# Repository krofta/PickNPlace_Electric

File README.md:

In general this repo contains all pcb schematics and layouts to build a simple
pick and place machine. All components are 24V compatible 
 
This repo contains the development of a computer vision modul
with STM32H7. It works as an automomous modul, wich communicates via can
bus. The images are captured via OV7670 camera. The modul has an external RAM of
8Mb zu make shure enough RAM is acessable to perform image processing.
 
PCB for the feeders:
Feeders are inspired by RepoPNP from Simun Huber:
https://github.com/Scavenger18/RepoPNP

The feeders will get some modification: cheaper micro controller from STmicroelectronics and 
prettier edge cut of the PCB plus mondifications of the drills to have another option to mount 
the procket motor with additional bearing.

Controller Module mith STM32F4 to execute simple reduced GCODE. Not shure if I will use 3D-printing like gcode or 
a very simple own format. The main board is capable to receive commands via virtual com port. 
It communicates with:
-Stepper board via GPIO and single wire
-Computer vision modules via CAN-bus(upside down and downside up) to find fiducials 
 and notice the xy-offset and rotation of an picket IC
-Feeders via CAN-bus

Stepper-Board: Just simple board with 4 Trinamic stepper drivers and connectors

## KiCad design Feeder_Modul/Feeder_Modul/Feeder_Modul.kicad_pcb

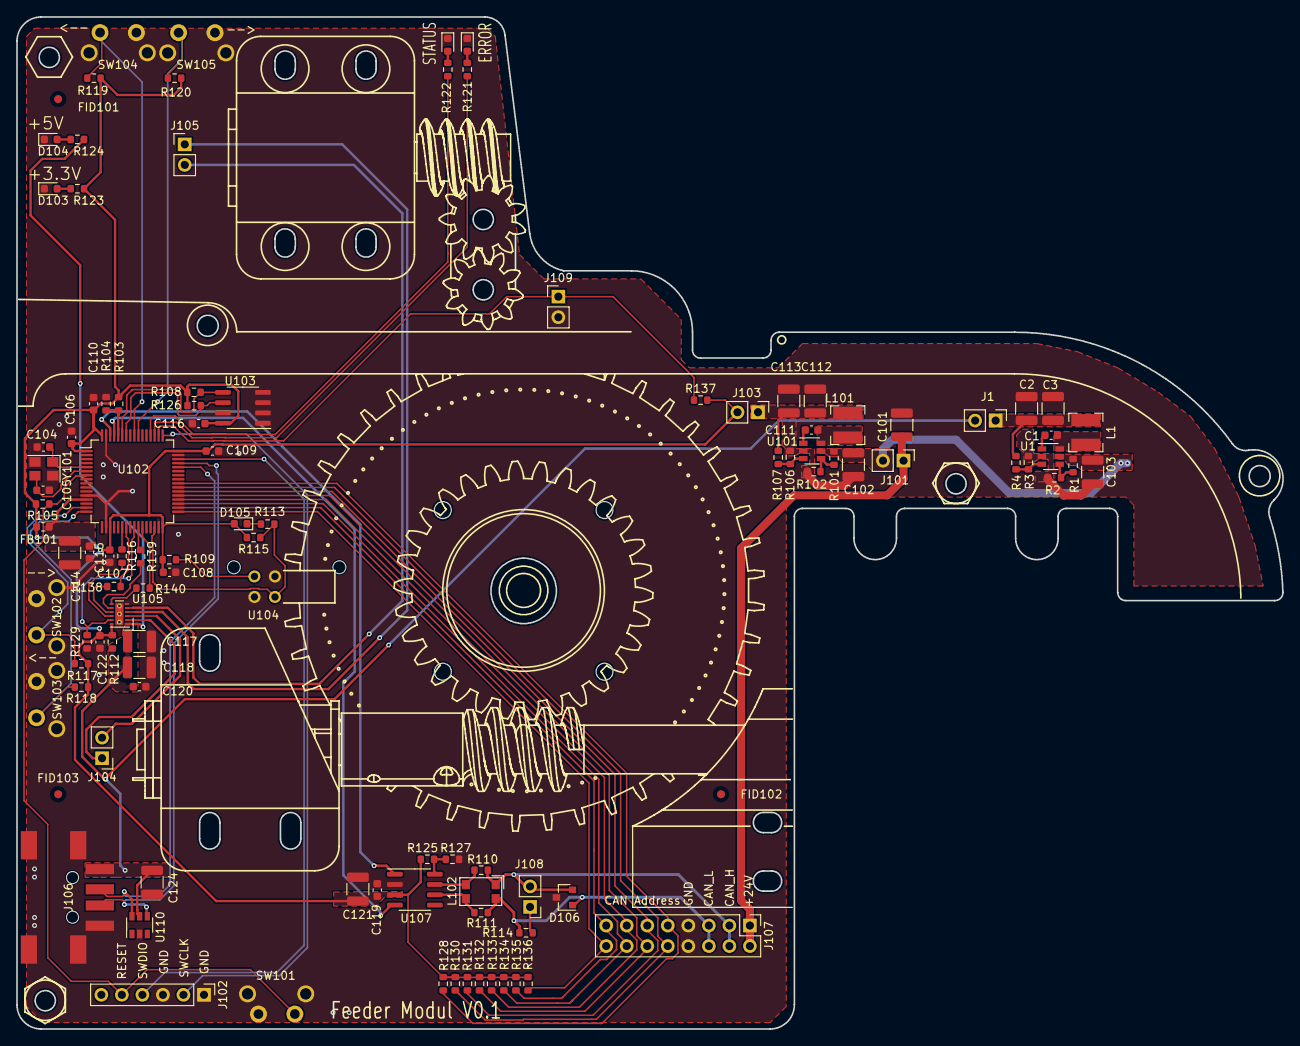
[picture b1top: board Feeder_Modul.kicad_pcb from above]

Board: 2 copper layers, 156.6 x 125.2 mm, 110 parts (0 on the bottom side), 69 nets.

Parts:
C1, C106, C107, C108, C109, C110, C111, C115, C116, C119, C120, C122: 100n 50V; C_0603_1608Metric
C2, C3, C101, C102, C103, C112, C113, C114, C117, C118, C121, C124: 10u 50V; C_1210_3225Metric
C104, C105: 18p; C_0603_1608Metric
D101: LED_red; LED_0603_1608Metric
D102: LED_green; LED_0603_1608Metric
D103, D104, D105: LED_Blue; LED_0603_1608Metric
D106: SM24CANA-02HTG; SOT-23
FB101: 70R; L_0603_1608Metric
FID101, FID102, FID103: Fiducial; Fiducial_1mm_Mask2mm
J1, J101, J103, J104, J105, J108, J109: Conn_02x01; PinHeader_1x02_P2.54mm_Vertical
J102: Conn_01x06_Male; PinHeader_1x06_P2.54mm_Vertical
J106: WE_629104190121; WE629104190121
J107: Conn_02x07_Odd_Even; PinHeader_2x08_P2.54mm_Vertical
L1, L101: 12u SRN4018; L_Bourns-SRN4018
L102: DNP; L_CommonModeChoke_Coilcraft_1812CAN
R1, R2, R101, R102, R107: 51K; R_0603_1608Metric
R3, R106: 22K1; R_0603_1608Metric
R4, R128, R130, R131, R132, R133, R134, R135, R136: 88K7; R_0603_1608Metric
R103, R112, R125: DNP; R_0603_1608Metric
R104, R105, R115, R117, R118, R119, R120, R129, R137: 10K; R_0603_1608Metric
R108, R116, R121, R122, R123, R124, R126, R127, R138, R139, R140: 1k; R_0603_1608Metric
R109, R114: 120R; R_0603_1608Metric
R110, R111: 0R; R_0603_1608Metric
R113: 1K; R_0603_1608Metric
SW101, SW102, SW103, SW104, SW105: SW_Push; TactileSwitchLCSC
U1, U101: TPS560430; SOT-23-6
U102: STM32F105R8Tx; LQFP-64_10x10mm_P0.5mm
U103: M24C01-WMN; SOIC-8_3.9x4.9mm_P1.27mm
U104: TCST5250
U105: DRV8835; WSON-12-1EP_3x2mm_P0.5mm_EP1x2.65_ThermalVias
U106: Panasonic_ESE22; Empty
U107: SN65HVD230; SOIC-8_3.9x4.9mm_P1.27mm
U108, U109: N20_DC_Motor; Empty
U110: SRV05-4; SOT-23-6
Y101: 8MHz; Crystal_SMD_3225-4Pin_3.2x2.5mm

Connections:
+3V3: C106.1, C107.2, C108.1, C109.2, C110.1, C116.1, C119.1, C121.1, C122.1, D105.2, FB101.2, J103.2, R103.2, R105.2, R108.2, R109.2, R112.2, R115.2, R117.2, R118.2, R119.2, R120.2, R123.2, R125.2, R126.2, R128.2, R130.2, R131.2, R132.2, R133.2, R134.2, R135.2, R136.2, R137.2, U102.1, U102.19, U102.32, U102.48, U102.64, U103.8, U105.12, U107.3
+5V: C117.1, C118.1, C120.1, C124.1, J1.2, J106.1, R112.1, R124.2, U105.1, U110.5
+24V: C101.1, J101.1, J107.1, J107.2
/ADDR0: J107.9, R128.1, U102.40
/ADDR1: J107.10, R130.1, U102.39
/ADDR2: J107.11, R131.1, U102.38
/ADDR3: J107.12, R132.1, U102.37
/ADDR4: J107.13, R133.1, U102.36
/ADDR5: J107.14, R134.1, U102.35
/ADDR6: J107.15, R135.1, U102.34
/ADDR7: J107.16, R136.1, U102.33
/BTN_SBACK: R119.1, SW104.2, U102.56
/BTN_SFOR: R120.1, SW105.2, U102.55
/BTN_TBACK: R117.1, SW102.2, U102.15
/BTN_TFOR: R118.1, SW103.2, U102.16
/CAN1_H: D106.2, J107.3, J107.4, J108.2, L102.2, R110.1
/CAN1_L: D106.1, J107.5, J107.6, L102.4, R111.2, R114.2
/CAN1_RX: U102.61, U107.4
/CAN1_TX: U102.62, U107.1
/ENC_OUT: R113.1, R115.1, U102.30, U104.4
/I2C1_SCL: R126.1, U102.58, U103.6
/I2C1_SDA: R108.1, U102.59, U103.5
/LED_error: R121.2, U102.51
/LED_status: R122.2, U102.52
/MODE: R129.2, U102.25, U105.11
/NRST: J102.5, R105.1, SW101.2, U102.7
/PA6: R116.2, U102.22
/PA7: R138.1, U102.23
/PA13: J102.4, U102.46
/PA14: J102.2, U102.49
/PD0: C104.1, U102.5, Y101.1
/PD1: C105.1, U102.6, Y101.3
/PWM_A: R116.1, U105.10
/PWM_B: R138.2, U105.9
/PWM_C: R139.1, U105.8
/PWM_D: R140.2, U105.7
/SprocketMotor+: J104.1, U105.2
/SprocketMotor-: J104.2, U105.3
/TAPE_MICROBTN: J109.1, R137.1, U102.50
/TIM3_CH3: R139.2, U102.26
/TIM3_CH4: R140.1, U102.27
/TapeMotor+: J105.1, U105.4
/TapeMotor-: J105.2, U105.5
/USB_OTG+: J106.3, U102.45, U110.4
/USB_OTG-: J106.2, U102.44, U110.6
GND: C2.2, C3.2, C101.2, C102.2, C103.2, C104.2, C105.2, C106.2, C107.1, C108.2, C109.1, C110.2, C112.2, C113.2, C114.2, C115.2, C116.2, C117.2, C118.2, C119.2, C120.2, C121.2, C122.2, C124.2, D101.1, D102.1, D103.1, D104.1, D106.3, J102.1, J102.3, J106.4, J106.5, J107.7, J107.8, J109.2, R2.1, R3.1, R102.1, R104.2, R106.1, R127.1, R129.1, SW101.1, SW101.3, SW102.1, SW102.3, SW103.1, SW103.3, SW104.1, SW104.3, SW105.1, SW105.3, U1.2, U101.2, U102.12, U102.18, U102.31, U102.47, U102.63, U103.1, U103.2, U103.3, U103.4, U103.7, U104.2, U104.3, U105.6, U105.13, U107.2, U110.2, Y101.2, Y101.4
unnamed: C1.1, L1.1, U1.6
unnamed: C1.2, U1.1
unnamed: C2.1, C3.1, J1.1, L1.2, R4.2
unnamed: C102.1, C103.1, J101.2, R1.1, R101.1, U1.5, U101.5
unnamed: C111.1, L101.1, U101.6
unnamed: C111.2, U101.1
unnamed: C112.1, C113.1, J103.1, L101.2, R107.2
unnamed: C114.1, C115.1, FB101.1, U102.13
unnamed: D101.2, R121.1
unnamed: D102.2, R122.1
unnamed: D103.2, R123.1
unnamed: D104.2, R124.1
unnamed: D105.1, R113.2
unnamed: J108.1, R114.1
unnamed: L102.1, R110.2, U107.7
unnamed: L102.3, R111.1, U107.6
unnamed: R1.2, R2.2, U1.4
unnamed: R3.2, R4.1, U1.3
unnamed: R101.2, R102.2, U101.4
unnamed: R103.1, R104.1, U102.60
unnamed: R106.2, R107.1, U101.3
unnamed: R109.1, U104.1
unnamed: R125.1, R127.2, U107.8

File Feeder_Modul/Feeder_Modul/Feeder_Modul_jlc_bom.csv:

Comment,Designator,Footprint,LCSC Part #
"100n 50V Unpolarized capacitor, small symbol","C1,C106,C107,C108,C109,C110,C111,C115,C116,C119,C120,C122",C_0603_1608Metric,C282519
"10u 50V Unpolarized capacitor, small symbol","C2,C3,C101,C102,C103,C112,C113,C114,C117,C118,C121,C124",C_1210_3225Metric,C1849
"18p Unpolarized capacitor, small symbol","C104,C105",C_0603_1608Metric,C258467
"LED_red Light emitting diode, small symbol",D101,LED_0603_1608Metric,C118330
"LED_green Light emitting diode, small symbol",D102,LED_0603_1608Metric,C205443
"LED_Blue Light emitting diode, small symbol","D103,D104,D105",LED_0603_1608Metric,C192317
"70R Ferrite bead, small symbol",FB101,L_0603_1608Metric,C513774
"Conn_02x01 Generic connector, single row, 01x02, script generated (kicad-library-utils/schlib/autogen/connector/)","J1,J101,J103,J104,J105,J108,J109",PinHeader_1x02_P2.54mm_Vertical,C358684
WE_629104190121 ,J106,WE629104190121,C718026
"Conn_02x07_Odd_Even Generic connector, double row, 02x07, odd/even pin numbering scheme (row 1 odd numbers, row 2 even numbers), script generated (kicad-library-utils/schlib/autogen/connector/)",J107,PinHeader_2x07_P2.54mm_Horizontal,C146608
"12u  SRN4018 Inductor, small symbol","L1,L101",L_Bourns-SRN4018,C354591 
"51K Resistor, small symbol","R1,R2,R101,R102,R107",R_0603_1608Metric,C384211
"22K1 Resistor, small symbol","R3,R106",R_0603_1608Metric,C137768
"88K7 Resistor, small symbol","R4,R128,R130,R131,R132,R133,R134,R135,R136",R_0603_1608Metric,C163418
"10K Resistor, small symbol","R104,R105,R115,R117,R118,R119,R120,R129,R137",R_0603_1608Metric,C99198
"1k Resistor, small symbol","R108,R109,R121,R122,R123,R124,R126,R127",R_0603_1608Metric,C21190
"0R Resistor, small symbol","R110,R111",R_0603_1608Metric,C384298
"1K Resistor, small symbol",R113,R_0603_1608Metric,C21190
"120R Resistor, small symbol",R114,R_0603_1608Metric,C114681
"SW_Push Push button switch, generic, two pins","SW101,SW102,SW103,SW104,SW105",TactileSwitchLCSC,C455137
TPS560430 ,"U1,U101",SOT-23-6,C524782
"STM32F105R8Tx ARM Cortex-M3 MCU, 64KB flash, 64KB RAM, 72MHz, 2-3.6V, 51 GPIO, LQFP-64",U102,LQFP-64_10x10mm_P0.5mm,C80986
"M24C01-WMN 1Kb (128x8) I2C Serial EEPROM, 2.5-5.5V, SOIC-8",U103,SOIC-8_3.9x4.9mm_P1.27mm,C7996
DRV8835 ,U105,WSON-12-1EP_3x2mm_P0.5mm_EP1x2.65_ThermalVias,C129328
"SN65HVD230 CAN Bus Transceivers, 3.3V, 1Mbps, Low-Power capabilities, SOIC-8",U107,SOIC-8_3.9x4.9mm_P1.27mm,C12084
"48MHz Four pin crystal, GND on pins 2 and 4",Y101,Crystal_SMD_3225-4Pin_3.2x2.5mm,C389928

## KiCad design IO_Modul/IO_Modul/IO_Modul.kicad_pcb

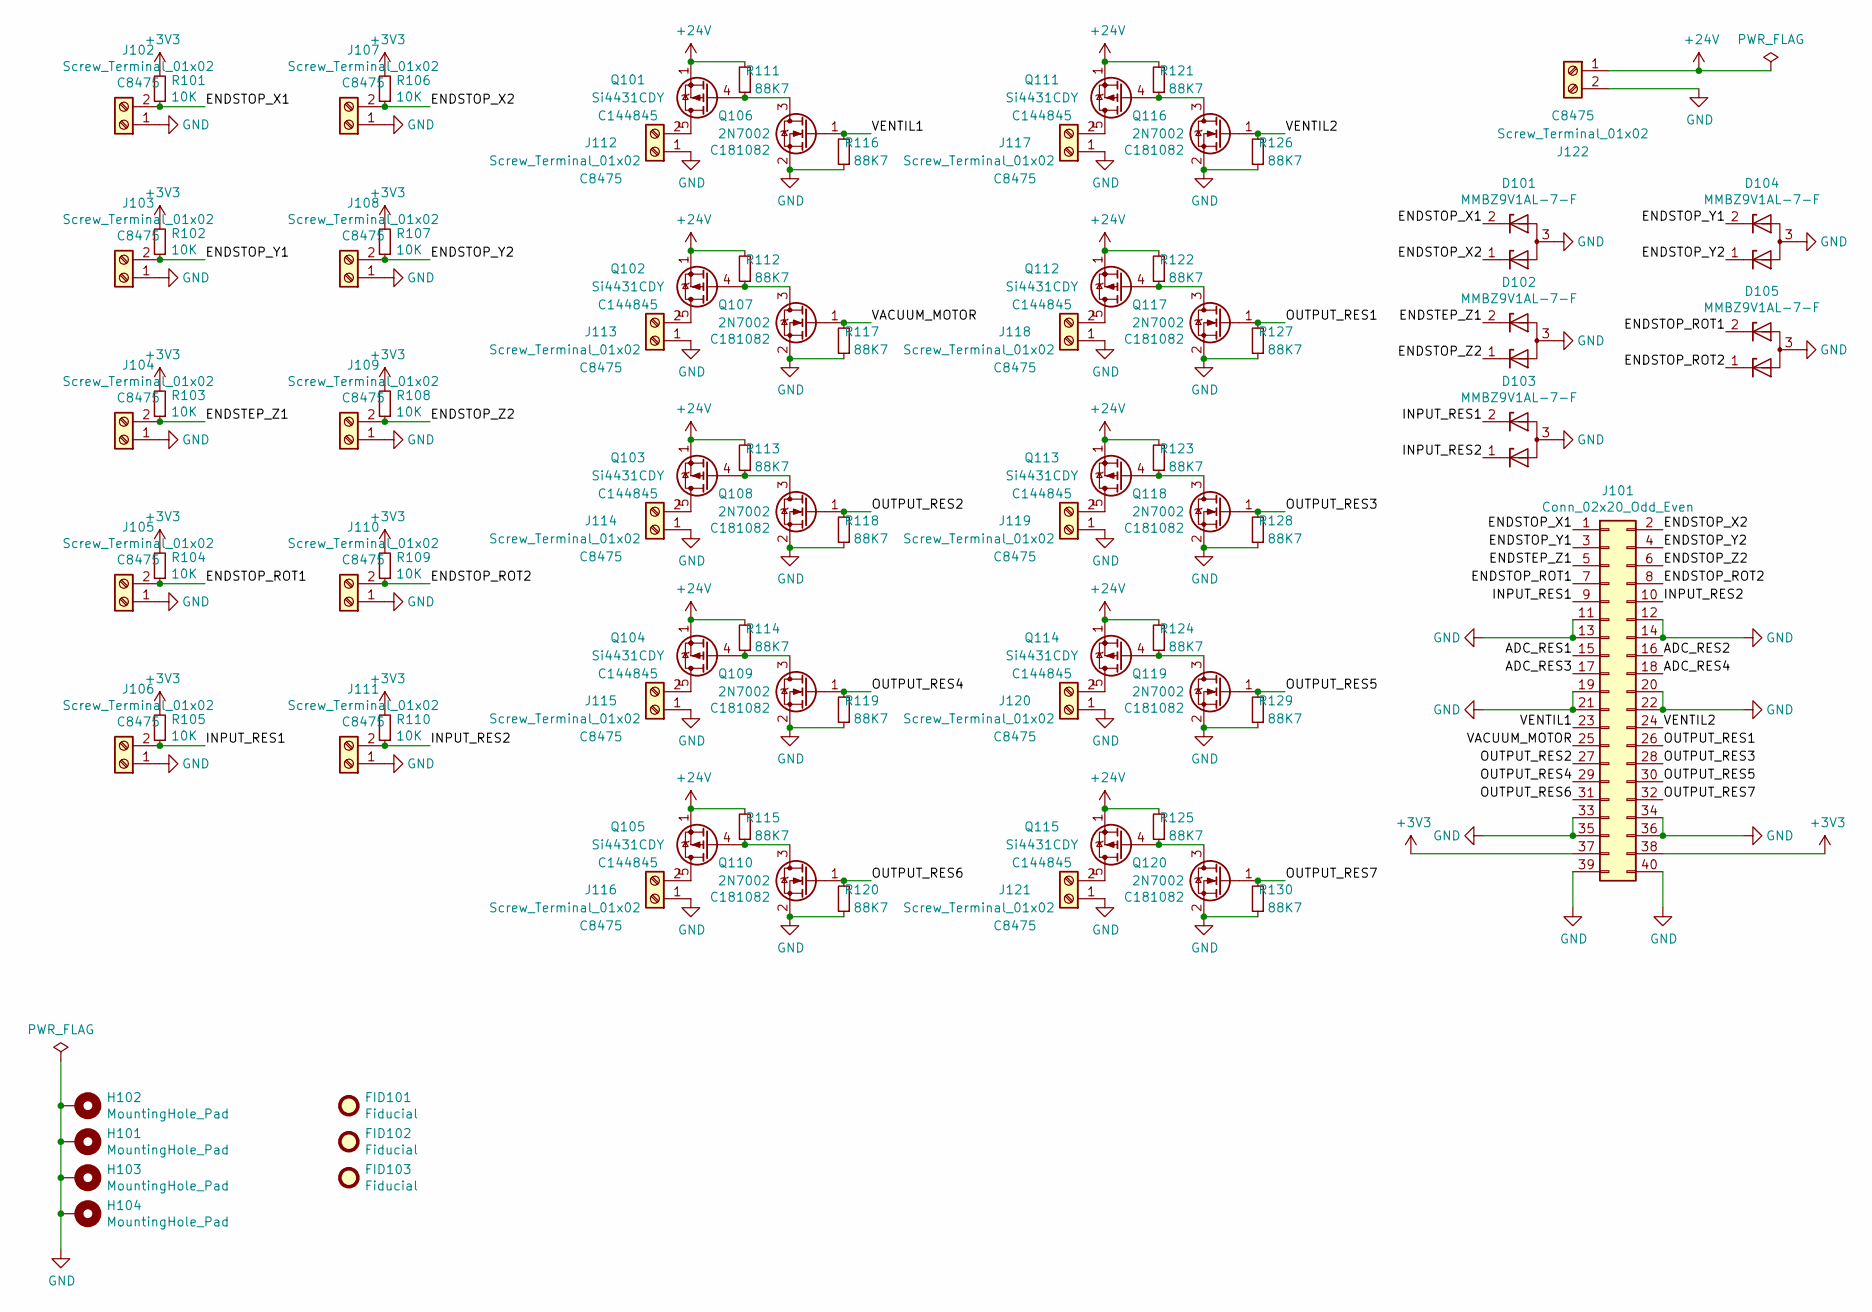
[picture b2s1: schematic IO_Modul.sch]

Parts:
D101, D102, D103, D104, D105: MMBZ9V1AL-7-F; SOT-23; LCSC C460913
FID101, FID102, FID103: Fiducial; Fiducial_1mm_Mask2mm
H101, H102, H103, H104: MountingHole_Pad; MountingHole_3.2mm_M3_Pad_Via; LCSC 0
J101: Conn_02x20_Odd_Even; PinHeader_2x20_P2.54mm_Vertical; LCSC C601944
J102, J103, J104, J105, J106, J107, J108, J109, J110, J111, J112, J113, J114, J115, J116, J117, J118, J119, J120, J121, J122: Screw_Terminal_01x02; TerminalBlock_RND_205-00045_1x02_P5.00mm_Horizontal; LCSC C8475
Q101, Q102, Q103, Q104, Q105, Q111, Q112, Q113, Q114, Q115: Si4431CDY; SOIC-8_3.9x4.9mm_P1.27mm; LCSC C144845
Q106, Q107, Q108, Q109, Q110, Q116, Q117, Q118, Q119, Q120: 2N7002; SOT-23; LCSC C181082
R101, R102, R103, R104, R105, R106, R107, R108, R109, R110: 10K; R_0603_1608Metric; LCSC C99198
R111, R112, R113, R114, R115, R116, R117, R118, R119, R120, R121, R122, R123, R124, R125, R126, R127, R128, R129, R130: 88K7; R_0603_1608Metric; LCSC C163418

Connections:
+3V3: J101.37, J101.38, R101.2, R102.2, R103.2, R104.2, R105.2, R106.2, R107.2, R108.2, R109.2, R110.2; also elsewhere on the board
+24V: J122.1, Q101.1 (D), Q101.2 (D), Q101.3 (D), Q102.1 (D), Q102.2 (D), Q102.3 (D), Q103.1 (D), Q103.2 (D), Q103.3 (D), Q104.1 (D), Q104.2 (D), Q104.3 (D), Q105.1 (D), Q105.2 (D), Q105.3 (D), Q111.1 (D), Q111.2 (D), Q111.3 (D), Q112.1 (D), Q112.2 (D), Q112.3 (D), Q113.1 (D), Q113.2 (D), Q113.3 (D), Q114.1 (D), Q114.2 (D), Q114.3 (D), Q115.1 (D), Q115.2 (D), Q115.3 (D), R111.2, R112.2, R113.2, R114.2, R115.2, R121.2, R122.2, R123.2, R124.2, R125.2
/ADC_RES1: J101.15; also elsewhere on the board
/ADC_RES2: J101.16; also elsewhere on the board
/ADC_RES3: J101.17; also elsewhere on the board
/ADC_RES4: J101.18; also elsewhere on the board
/ENDSTEP_Z1: D102.2 (K), J101.5, J104.2, R103.1
/ENDSTOP_ROT1: D105.2 (K), J101.7, J105.2, R104.1
/ENDSTOP_ROT2: D105.1 (K), J101.8, J110.2, R109.1
/ENDSTOP_X1: D101.2 (K), J101.1, J102.2, R101.1
/ENDSTOP_X2: D101.1 (K), J101.2, J107.2, R106.1
/ENDSTOP_Y1: D104.2 (K), J101.3, J103.2, R102.1
/ENDSTOP_Y2: D104.1 (K), J101.4, J108.2, R107.1
/ENDSTOP_Z2: D102.1 (K), J101.6, J109.2, R108.1
/INPUT_RES1: D103.2 (K), J101.9, J106.2, R105.1
/INPUT_RES2: D103.1 (K), J101.10, J111.2, R110.1
/OUTPUT_RES1: J101.26, Q117.1 (G), R127.2
/OUTPUT_RES2: J101.27, Q108.1 (G), R118.2
/OUTPUT_RES3: J101.28, Q118.1 (G), R128.2
/OUTPUT_RES4: J101.29, Q109.1 (G), R119.2
/OUTPUT_RES5: J101.30, Q119.1 (G), R129.2
/OUTPUT_RES6: J101.31, Q110.1 (G), R120.2
/OUTPUT_RES7: J101.32, Q120.1 (G), R130.2
/VACUUM_MOTOR: J101.25, Q107.1 (G), R117.2
/VENTIL1: J101.23, Q106.1 (G), R116.2
/VENTIL2: J101.24, Q116.1 (G), R126.2
GND: D101.3 (A), D102.3 (A), D103.3 (A), D104.3 (A), D105.3 (A), H101.1, H102.1, H103.1, H104.1, J101.11, J101.12, J101.13, J101.14, J101.19, J101.20, J101.21, J101.22, J101.33, J101.34, J101.35, J101.36, J101.39, J101.40, J102.1, J103.1, J104.1, J105.1, J106.1, J107.1, J108.1, J109.1, J110.1, J111.1, J112.1, J113.1, J114.1, J115.1, J116.1, J117.1, J118.1, J119.1, J120.1, J121.1, J122.2, Q106.2 (S), Q107.2 (S), Q108.2 (S), Q109.2 (S), Q110.2 (S), Q116.2 (S), Q117.2 (S), Q118.2 (S), Q119.2 (S), Q120.2 (S), R116.1, R117.1, R118.1, R119.1, R120.1, R126.1, R127.1, R128.1, R129.1, R130.1; also elsewhere on the board
unnamed: J112.2, Q101.5 (S), Q101.6 (S), Q101.7 (S), Q101.8 (S)
unnamed: J113.2, Q102.5 (S), Q102.6 (S), Q102.7 (S), Q102.8 (S)
unnamed: J114.2, Q103.5 (S), Q103.6 (S), Q103.7 (S), Q103.8 (S)
unnamed: J115.2, Q104.5 (S), Q104.6 (S), Q104.7 (S), Q104.8 (S)
unnamed: J116.2, Q105.5 (S), Q105.6 (S), Q105.7 (S), Q105.8 (S)
unnamed: J117.2, Q111.5 (S), Q111.6 (S), Q111.7 (S), Q111.8 (S)
unnamed: J118.2, Q112.5 (S), Q112.6 (S), Q112.7 (S), Q112.8 (S)
unnamed: J119.2, Q113.5 (S), Q113.6 (S), Q113.7 (S), Q113.8 (S)
unnamed: J120.2, Q114.5 (S), Q114.6 (S), Q114.7 (S), Q114.8 (S)
unnamed: J121.2, Q115.5 (S), Q115.6 (S), Q115.7 (S), Q115.8 (S)
unnamed: Q101.4 (G), Q106.3 (D), R111.1
unnamed: Q102.4 (G), Q107.3 (D), R112.1
unnamed: Q103.4 (G), Q108.3 (D), R113.1
unnamed: Q104.4 (G), Q109.3 (D), R114.1
unnamed: Q105.4 (G), Q110.3 (D), R115.1
unnamed: Q111.4 (G), Q116.3 (D), R121.1
unnamed: Q112.4 (G), Q117.3 (D), R122.1
unnamed: Q113.4 (G), Q118.3 (D), R123.1
unnamed: Q114.4 (G), Q119.3 (D), R124.1
unnamed: Q115.4 (G), Q120.3 (D), R125.1

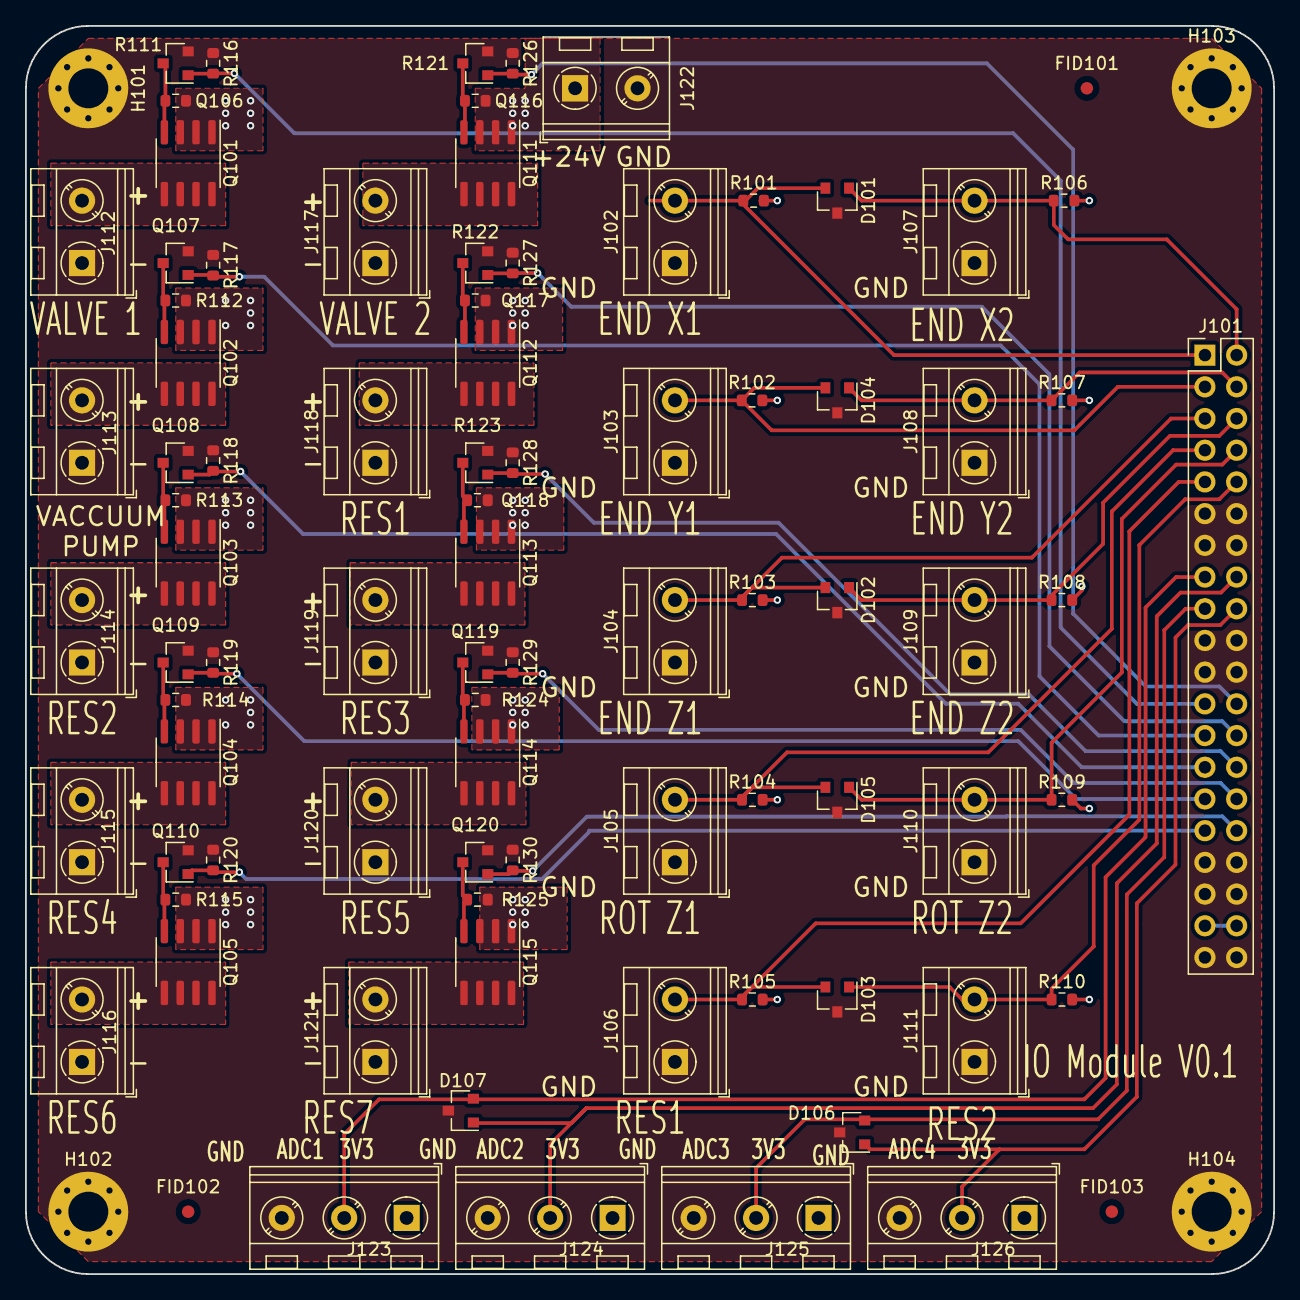
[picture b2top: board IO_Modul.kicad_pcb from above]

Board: 4 copper layers, 100.0 x 100.0 mm, 90 parts (0 on the bottom side), 47 nets.

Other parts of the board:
D106, D107: MMBZ9V1AL-7-F; SOT-23
J123, J124, J125, J126: Screw_Terminal_01x03; TerminalBlock_RND_205-00046_1x03_P5.00mm_Horizontal

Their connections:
+3V3: J123.1, J124.1, J125.1, J126.1; also elsewhere on the board
/ADC_RES1: D107.2, J123.2; also elsewhere on the board
/ADC_RES2: D107.1, J124.2; also elsewhere on the board
/ADC_RES3: D106.2, J125.2; also elsewhere on the board
/ADC_RES4: D106.1, J126.2; also elsewhere on the board
GND: D106.3, D107.3, J123.3, J124.3, J125.3, J126.3; also elsewhere on the board

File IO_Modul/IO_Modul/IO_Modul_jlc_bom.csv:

Comment,Designator,Footprint,LCSC Part #,Quantity
"Conn_02x20_Odd_Even Generic connector, double row, 02x20, odd/even pin numbering scheme (row 1 odd numbers, row 2 even numbers), script generated (kicad-library-utils/schlib/autogen/connector/)",J101,PinHeader_2x20_P2.54mm_Vertical,C601944,1
"Screw_Terminal_01x02 Generic screw terminal, single row, 01x02, script generated (kicad-library-utils/schlib/autogen/connector/)","J102,J103,J104,J105,J106,J107,J108,J109,J110,J111,J112,J113,J114,J115,J116,J117,J118,J119,J120,J121,J122",TerminalBlock_RND_205-00045_1x02_P5.00mm_Horizontal,C8475,21
"Si4431CDY P-MOSFET transistor, drain/gate/source","Q101,Q102,Q103,Q104,Q105,Q111,Q112,Q113,Q114,Q115",SOIC-8_3.9x4.9mm_P1.27mm,C144845,10
"2N7002 0.115A Id, 60V Vds, N-Channel MOSFET, SOT-23","Q106,Q107,Q108,Q109,Q110,Q116,Q117,Q118,Q119,Q120",SOT-23,C181082,10
"10K Resistor, small symbol","R101,R102,R103,R104,R105,R106,R107,R108,R109,R110",R_0603_1608Metric,C99198,10
"88K7 Resistor, small symbol","R111,R112,R113,R114,R115,R116,R117,R118,R119,R120,R121,R122,R123,R124,R125,R126,R127,R128,R129,R130",R_0603_1608Metric,C163418,20

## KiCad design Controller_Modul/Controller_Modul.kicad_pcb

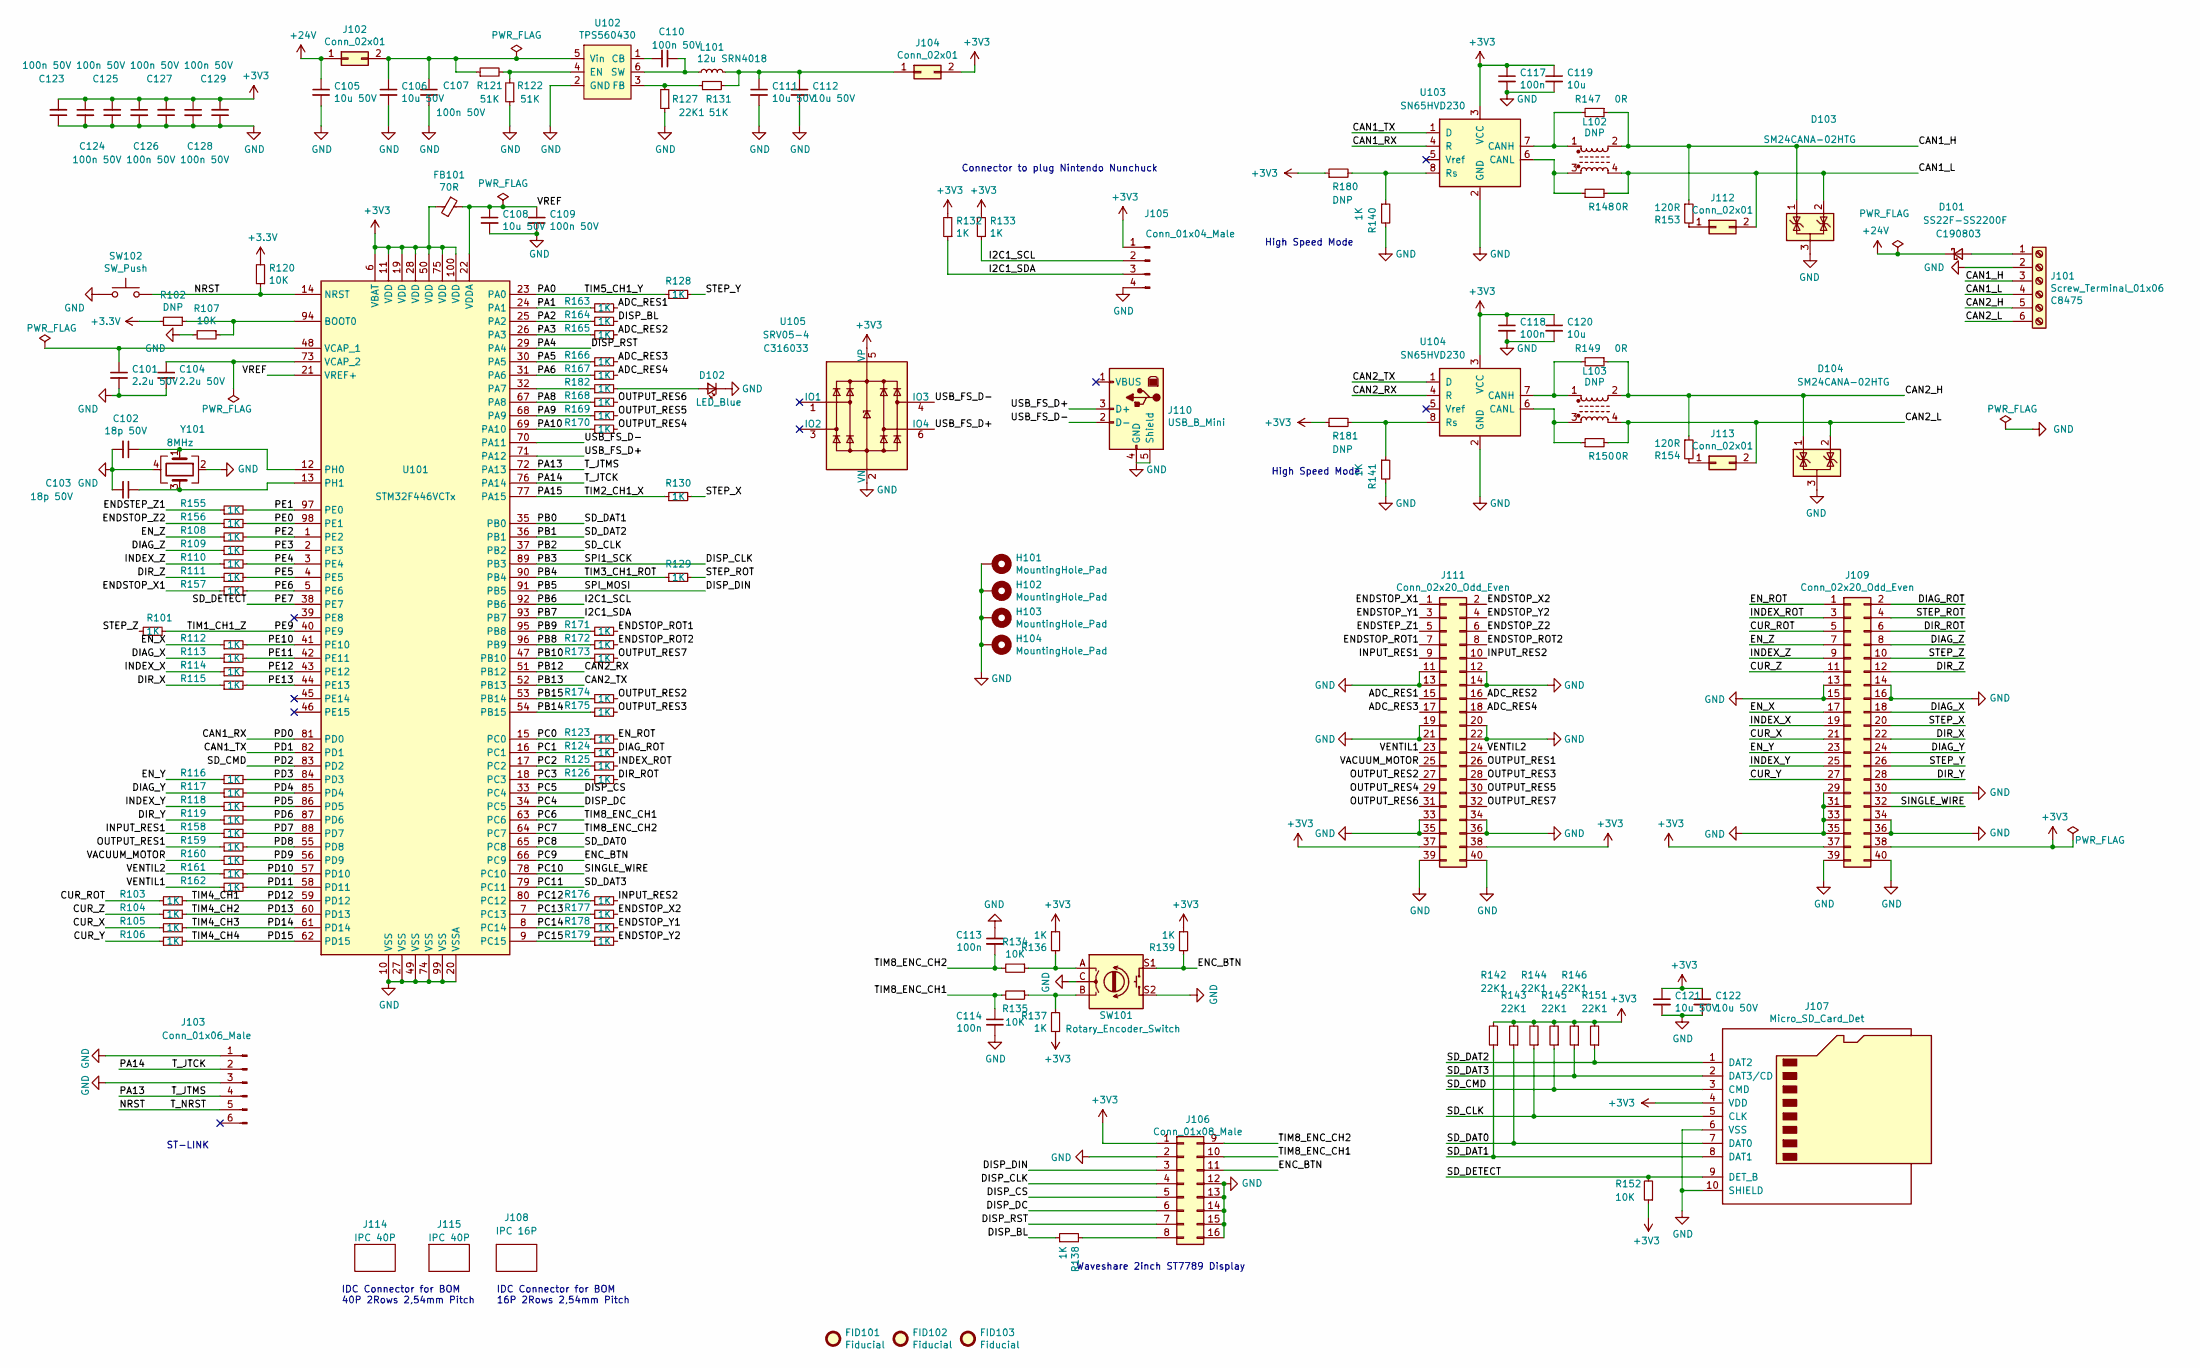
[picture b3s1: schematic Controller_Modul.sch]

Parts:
C101, C104: 2.2u 50V; C_1210_3225Metric; LCSC C696854
C102, C103: 18p 50V; C_0603_1608Metric; LCSC C258467
C105, C106, C108, C111, C112, C121, C122: 10u 50V; C_1210_3225Metric; LCSC C1849
C107, C109, C110, C123, C124, C125, C126, C127, C128, C129: 100n 50V; C_0603_1608Metric; LCSC C282519
C113, C114, C117, C118: 100n; C_0603_1608Metric; LCSC C83060
C119, C120: 10u; C_1210_3225Metric; LCSC C1849
D101: SS22F-SS2200F; D_SMA; LCSC C190803
D102: LED_Blue; LED_0603_1608Metric; LCSC C192317
D103, D104: SM24CANA-02HTG; SOT-23; LCSC C151236
FB101: 70R; L_0603_1608Metric; LCSC C513774
FID101, FID102, FID103: Fiducial; Fiducial_1mm_Mask2mm; LCSC 0
H101, H102, H103, H104: MountingHole_Pad; MountingHole_3.2mm_M3_Pad_Via; LCSC 0
J101: Screw_Terminal_01x06; TerminalBlock_RND_205-00049_1x06_P5.00mm_Horizontal; LCSC C8475
J102, J104, J112, J113: Conn_02x01; PinHeader_1x02_P2.54mm_Vertical; LCSC C358684
J103: Conn_01x06_Male; PinHeader_1x06_P2.54mm_Vertical; LCSC 0
J105: Conn_01x04_Male; PinHeader_1x04_P2.54mm_Vertical; LCSC 0
J106: Conn_01x08_Male; ST7789_Waveshare2; LCSC C3406
J107: Micro_SD_Card_Det; TF-115-BCP9; LCSC C720505
J108: IPC 16P; Empty; LCSC C8372
J109, J111: Conn_02x20_Odd_Even; PinHeader_2x20_P2.54mm_Vertical; LCSC C601944
J110: USB_B_Mini; USB_B_OST_USB-B1HSxx_Horizontal; LCSC C46392
J114, J115: IPC 40P; Empty; LCSC C601933
L101: 12u SRN4018; L_Bourns-SRN4018; LCSC C354591
L102, L103: DNP; L_CommonModeChoke_Coilcraft_1812CAN; LCSC 0
R101, R103, R104, R105, R106, R108, R109, R110, R111, R112, R113, R114, R115, R116, R117, R118, R119, R123, R124, R125, R126, R128, R129, R130, R132, R133, R136, R137, R138, R139, R140, R141, R155, R156, R157, R158, R159, R160, R161, R162, R163, R164, R165, R166, R167, R168, R169, R170, R171, R172, R173, R174, R175, R176, R177, R178, R179, R182: 1K; R_0603_1608Metric; LCSC C14676
R102, R180, R181: DNP; R_0603_1608Metric; LCSC 0
R107, R120, R134, R135, R152: 10K; R_0603_1608Metric; LCSC C99198
R121, R122, R131: 51K; R_0603_1608Metric; LCSC C384211
R127, R142, R143, R144, R145, R146, R151: 22K1; R_0603_1608Metric; LCSC C137768
R147, R148, R149, R150: 0R; R_0603_1608Metric; LCSC C384298
R153, R154: 120R; R_0603_1608Metric; LCSC C114681
SW101: Rotary_Encoder_Switch; RotaryEncoder_Alps_EC11E-Switch_Vertical_H20mm_CircularMoun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; LCSC 0
SW102: SW_Push; TactileSwitchLCSC; LCSC C455137
U101: STM32F446VCTx; LQFP-100_14x14mm_P0.5mm; LCSC 0
U102: TPS560430; SOT-23-6; LCSC C524782
U103, U104: SN65HVD230; SOIC-8_3.9x4.9mm_P1.27mm; LCSC C12084
U105: SRV05-4; SOT-23-6; LCSC C316033
Y101: 8MHz; Crystal_SMD_3225-4Pin_3.2x2.5mm; LCSC C400090

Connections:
+24V: C105.1, D101.1 (K), J102.1
/ADC_RES1: J111.15, R163.2
/ADC_RES2: J111.16, R165.2
/ADC_RES3: J111.17, R166.2
/ADC_RES4: J111.18, R167.2
/CAN1_H: D103.1 (K), J101.3, L102.2, R147.1, R153.1
/CAN1_L: D103.2 (K), J101.4, J112.2, L102.4, R148.2
/CAN1_RX: U101.81 (PD0), U103.4 (R)
/CAN1_TX: U101.82 (PD1), U103.1 (D)
/CAN2_H: D104.1 (K), J101.5, L103.2, R149.1, R154.1
/CAN2_L: D104.2 (K), J101.6, J113.2, L103.4, R150.2
/CAN2_RX: U101.51 (PB12), U104.4 (R)
/CAN2_TX: U101.52 (PB13), U104.1 (D)
/CUR_ROT: J109.5, R103.1
/CUR_X: J109.21, R105.1
/CUR_Y: J109.27, R106.1
/CUR_Z: J109.11, R104.1
/DIAG_ROT: J109.2, R124.2
/DIAG_X: J109.18, R113.1
/DIAG_Y: J109.24, R117.1
/DIAG_Z: J109.8, R109.1
/DIR_ROT: J109.6, R126.2
/DIR_X: J109.22, R115.1
/DIR_Y: J109.28, R119.1
/DIR_Z: J109.12, R111.1
/DISP_BL: R138.1, R164.2
/DISP_CLK: J106.4, U101.89 (PB3)
/DISP_CS: J106.5, U101.33 (PC4)
/DISP_DC: J106.6, U101.34 (PC5)
/DISP_DIN: J106.3, U101.91 (PB5)
/DISP_RST: J106.7, U101.29 (PA4)
/ENC_BTN: J106.11, R139.2, SW101.S1, U101.66 (PC9)
/ENDSTEP_Z1: J111.5, R155.1
/ENDSTOP_ROT1: J111.7, R171.2
/ENDSTOP_ROT2: J111.8, R172.2
/ENDSTOP_X1: J111.1, R157.1
/ENDSTOP_X2: J111.2, R177.2
/ENDSTOP_Y1: J111.3, R178.2
/ENDSTOP_Y2: J111.4, R179.2
/ENDSTOP_Z2: J111.6, R156.1
/EN_ROT: J109.1, R123.2
/EN_X: J109.17, R112.1
/EN_Y: J109.23, R116.1
/EN_Z: J109.7, R108.1
/I2C1_SCL: J105.2, R133.1, U101.92 (PB6)
/I2C1_SDA: J105.3, R132.1, U101.93 (PB7)
/INDEX_ROT: J109.3, R125.2
/INDEX_X: J109.19, R114.1
/INDEX_Y: J109.25, R118.1
/INDEX_Z: J109.9, R110.1
/INPUT_RES1: J111.9, R158.1
/INPUT_RES2: J111.10, R176.2
/NRST: J103.5, R120.1, SW102.2, U101.14 (NRST)
/OUTPUT_RES1: J111.26, R159.1
/OUTPUT_RES2: J111.27, R174.2
/OUTPUT_RES3: J111.28, R175.2
/OUTPUT_RES4: J111.29, R170.2
/OUTPUT_RES5: J111.30, R169.2
/OUTPUT_RES6: J111.31, R168.2
/OUTPUT_RES7: J111.32, R173.2
/PA0: R128.1, U101.23 (PA0)
/PA1: R163.1, U101.24 (PA1)
/PA2: R164.1, U101.25 (PA2)
/PA3: R165.1, U101.26 (PA3)
/PA5: R166.1, U101.30 (PA5)
/PA6: R167.1, U101.31 (PA6)
/PA8: R168.1, U101.67 (PA8)
/PA9: R169.1, U101.68 (PA9)
/PA10: R170.1, U101.69 (PA10)
/PA13: J103.4, U101.72 (PA13)
/PA14: J103.2, U101.76 (PA14)
/PA15: R130.1, U101.77 (PA15)
/PB0: J107.8 (DAT1), R142.1, U101.35 (PB0)
/PB1: J107.1 (DAT2), R151.1, U101.36 (PB1)
/PB2: J107.5 (CLK), R144.1, U101.37 (PB2)
/PB4: R129.1, U101.90 (PB4)
/PB8: R172.1, U101.96 (PB9)
/PB9: R171.1, U101.95 (PB8)
/PB10: R173.1, U101.47 (PB10)
/PB14: R175.1, U101.54 (PB15)
/PB15: R174.1, U101.53 (PB14)
/PC0: R123.1, U101.15 (PC0)
/PC1: R124.1, U101.16 (PC1)
/PC2: R125.1, U101.17 (PC2)
/PC3: R126.1, U101.18 (PC3)
/PC6: C114.1, J106.10, R135.2, U101.63 (PC6)
/PC7: C113.2, J106.9, R134.2, U101.64 (PC7)
/PC8: J107.7 (DAT0), R143.1, U101.65 (PC8)
/PC10: J109.32, U101.78 (PC10)
/PC11: J107.2 (DAT3/CD), R146.1, U101.79 (PC11)
/PC12: R176.1, U101.80 (PC12)
/PC13: R177.1, U101.7 (PC13)
/PC14: R178.1, U101.8 (PC14)
/PC15: R179.1, U101.9 (PC15)
/PD2: J107.3 (CMD), R145.1, U101.83 (PD2)
/PD3: R116.2, U101.84 (PD3)
/PD4: R117.2, U101.85 (PD4)
/PD5: R118.2, U101.86 (PD5)
/PD6: R119.2, U101.87 (PD6)
/PD7: R158.2, U101.88 (PD7)
/PD8: R159.2, U101.55 (PD8)
/PD9: R160.2, U101.56 (PD9)
/PD10: R161.2, U101.57 (PD10)
/PD11: R162.2, U101.58 (PD11)
/PD12: R103.2, U101.59 (PD12)
/PD13: R104.2, U101.60 (PD13)
/PD14: R105.2, U101.61 (PD14)
/PD15: R106.2, U101.62 (PD15)
/PE0: R156.2, U101.98 (PE1)
/PE1: R155.2, U101.97 (PE0)
/PE2: R108.2, U101.1 (PE2)
/PE3: R109.2, U101.2 (PE3)
/PE4: R110.2, U101.3 (PE4)
/PE5: R111.2, U101.4 (PE5)
/PE6: R157.2, U101.5 (PE6)
/PE7: J107.9 (DET_B), R152.2, U101.38 (PE7)
/PE9: R101.2, U101.40 (PE9)
/PE10: R112.2, U101.41 (PE10)
/PE11: R113.2, U101.42 (PE11)
/PE12: R114.2, U101.43 (PE12)
/PE13: R115.2, U101.44 (PE13)
/STEP_ROT: J109.4, R129.2
/STEP_X: J109.20, R130.2
/STEP_Y: J109.26, R128.2
/STEP_Z: J109.10, R101.1
/USB_FS_D+: J110.3 (D+), U101.71 (PA12), U105.6 (IO4)
/USB_FS_D-: J110.2 (D-), U101.70 (PA11), U105.4 (IO3)
/VACUUM_MOTOR: J111.25, R160.1
/VENTIL1: J111.23, R162.1
/VENTIL2: J111.24, R161.1
/VREF: C108.1, C109.1, FB101.1, U101.21 (VREF+), U101.22 (VDDA)
GND: C101.2, C102.2, C103.2, C104.2, C105.2, C106.2, C107.2, C108.2, C109.2, C111.2, C112.2, C113.1, C114.2, C117.2, C118.2, C119.2, C120.2, C121.2, C122.2, C123.1, C124.2, C125.1, C126.2, C127.1, C128.2, C129.1, D102.1 (K), D103.3 (A), D104.3 (A), H101.1, H102.1, H103.1, H104.1, J101.2, J103.1, J103.3, J105.4, J106.2, J106.12, J106.13, J106.14, J106.15, J106.16, J107.6 (VSS), J107.10 (SHIELD), J109.13, J109.14, J109.15, J109.16, J109.29, J109.30, J109.31, J109.33, J109.34, J109.35, J109.36, J109.39, J109.40, J110.4 (GND), J110.5 (Shield), J111.11, J111.12, J111.13, J111.14, J111.19, J111.20, J111.21, J111.22, J111.33, J111.34, J111.35, J111.36, J111.39, J111.40, R107.2, R122.1, R127.1, R140.2, R141.2, SW101.C, SW101.S2, SW102.1, U101.10 (VSS), U101.20 (VSSA), U101.27 (VSS), U101.49 (VSS), U101.74 (VSS), U101.99 (VSS), U102.2 (GND), U103.2 (GND), U104.2 (GND), U105.2 (VN), Y101.2, Y101.4
unnamed: C101.1, U101.48 (VCAP_1)
unnamed: C102.1, U101.12 (PH0), Y101.1
unnamed: C103.1, U101.13 (PH1), Y101.3
unnamed: C104.1, U101.73 (VCAP_2)
unnamed: C106.1, C107.1, J102.2, R121.1, U102.5 (Vin)
unnamed: C110.1, L101.1, U102.6 (SW)
unnamed: C110.2, U102.1 (CB)
unnamed: C111.1, C112.1, J104.1, L101.2, R131.2
unnamed: D101.2 (A), J101.1
unnamed: D102.2 (A), R182.2
unnamed: J106.8, R138.2
unnamed: J112.1, R153.2
unnamed: J113.1, R154.2
unnamed: L102.1, R147.2, U103.7 (CANH)
unnamed: L102.3, R148.1, U103.6 (CANL)
unnamed: L103.1, R149.2, U104.7 (CANH)
unnamed: L103.3, R150.1, U104.6 (CANL)
unnamed: R102.1, R107.1, U101.94 (BOOT0)
unnamed: R121.2, R122.2, U102.4 (EN)
unnamed: R127.2, R131.1, U102.3 (FB)
unnamed: R134.1, R136.2, SW101.A
unnamed: R135.1, R137.2, SW101.B
unnamed: R140.1, R180.2, U103.8 (Rs)
unnamed: R141.1, R181.2, U104.8 (Rs)
unnamed: R182.1, U101.32 (PA7)

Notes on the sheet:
ST-LINK
Waveshare 2inch ST7789 Display
Connector to plug Nintendo Nunchuck
High Speed Mode
IDC Connector for BOM 16P 2Rows 2,54mm Pitch
IDC Connector for BOM 40P 2Rows 2,54mm Pitch

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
